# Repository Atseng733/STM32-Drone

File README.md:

# STM32 Drone
I program a drone from scratch using C++

# Hardware:

Microcontroller: STM32F103C8

IMU: MPU6050

Receiver: Flysky Fli14+

Transmitter: Flysky FS-i6

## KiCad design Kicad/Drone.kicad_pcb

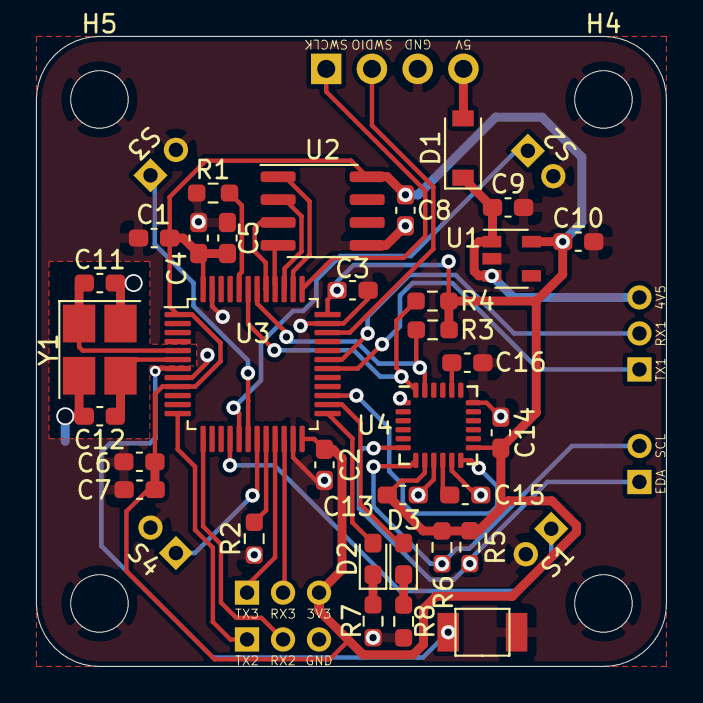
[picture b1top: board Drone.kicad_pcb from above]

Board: 2 copper layers, 35.0 x 35.0 mm, 46 parts (0 on the bottom side), 36 nets.

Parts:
C1, C2, C3, C4, C8: 100nF; C_0603_1608Metric_Pad1.08x0.95mm_HandSolder
C5: 4.7uF; C_0603_1608Metric_Pad1.08x0.95mm_HandSolder
C6, C13: 10nF; C_0603_1608Metric_Pad1.08x0.95mm_HandSolder
C7, C9, C10: 1uF; C_0603_1608Metric_Pad1.08x0.95mm_HandSolder
C11, C12: 12pF; C_0603_1608Metric_Pad1.08x0.95mm_HandSolder
C14, C15: .1uF; C_0603_1608Metric_Pad1.08x0.95mm_HandSolder
C16: 2.2nF; C_0603_1608Metric_Pad1.08x0.95mm_HandSolder
D1: ?; D_SOD-123
D2: Green; LED_0603_1608Metric_Pad1.05x0.95mm_HandSolder
D3: Red; LED_0603_1608Metric_Pad1.05x0.95mm_HandSolder
H3, H4, H5, H6: MountingHole; MountingHole_3.2mm_M3
J1: SWD; PinHeader_1x04_P2.54mm_Vertical
J2: UART1; PinHeader_1x03_P2.00mm_Vertical
J3: UART3; PinHeader_1x03_P2.00mm_Vertical
J4: UART2; PinHeader_1x03_P2.00mm_Vertical
J5: GYRO_AUX_I2C; PinHeader_1x02_P2.00mm_Vertical
R1, R2: 10k; R_0603_1608Metric_Pad0.98x0.95mm_HandSolder
R3, R4, R5, R6: 2.2k; R_0603_1608Metric_Pad0.98x0.95mm_HandSolder
R7, R8: 220; R_0603_1608Metric_Pad0.98x0.95mm_HandSolder
S1: S1; PinHeader_1x02_P2.00mm_Vertical
S2: S2; PinHeader_1x02_P2.00mm_Vertical
S3: S3; PinHeader_1x02_P2.00mm_Vertical
S4: S4; PinHeader_1x02_P2.00mm_Vertical
SW1: SW_MEC_5G; EVPBA
U1: MIC5504-3.3YM5; SOT-23-5
U2: 93CxxB; SOIC-8_3.9x4.9mm_P1.27mm
U3: STM32F103C8Tx; LQFP-48_7x7mm_P0.5mm
U4: MPU-6050; InvenSense_QFN-24_4x4mm_P0.5mm
Y1: 16 MHz; Crystal_SMD_3225-4Pin_3.2x2.5mm_HandSoldering

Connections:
4V5: C9.1, D1.1, J2.3, U1.1, U1.3
+3.3VA: C1.1, C2.1, C3.1, C4.1, C5.1, C6.1, C7.1, C8.2, C10.1, C13.1, C14.1, J3.3, R3.1, R4.1, R5.1, R6.1, U1.5, U2.8, U3.1, U3.9, U3.24, U3.36, U3.48, U4.8, U4.13
+5V: D1.2, J1.4
BOOT0: R1.1, U3.44
BOOT1: R2.1, U3.20
CS1: U2.1, U3.38
GND: C1.2, C2.2, C3.2, C4.2, C5.2, C6.2, C7.2, C8.1, C9.2, C10.2, C11.2, C12.2, C13.2, C14.2, C15.2, C16.2, H3.1, H4.1, H5.1, H6.1, J1.3, J4.3, R1.2, R2.2, R7.2, R8.2, S1.2, S2.2, S3.2, S4.2, SW1.1, U1.2, U2.5, U3.8, U3.23, U3.35, U3.47, U4.1, U4.9, U4.11, U4.18, Y1.2, Y1.4
GYRO_AUX_SCL: J5.2, R6.2, U4.7
GYRO_AUX_SDA: J5.1, R5.2, U4.6
GYRO_INT: U3.27, U4.12
HSE_IN: C11.1, U3.5, Y1.1
HSE_OUT: C12.1, U3.6, Y1.3
MISO1: U2.4, U3.40
MOSI1: U2.3, U3.41
MOTOR1_Signal: S1.1, U3.16
MOTOR2_Signal: S2.1, U3.17
MOTOR3_Signal: S3.1, U3.18
MOTOR4_Signal: S4.1, U3.19
NRST: SW1.2, U3.7
unnamed: C15.1, U4.10
unnamed: C16.1, U4.20
unnamed: D2.1, R7.1
unnamed: D2.2, U3.25
unnamed: D3.1, R8.1
unnamed: D3.2, U3.26
RX1: J2.2, U3.31
RX2: J4.2, U3.13
RX3: J3.2, U3.22
SCK1: U2.2, U3.39
SCL1: R3.2, U3.42, U4.23
SDA1: R4.2, U3.43, U4.24
SWCLK: J1.1, U3.37
SWDIO: J1.2, U3.34
TX1: J2.1, U3.30
TX2: J4.1, U3.12
TX3: J3.1, U3.21

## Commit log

2020-06-18 Create Self-balancing Drone
2020-06-22 add esp8266 project
2020-06-23 Add sigGen project
2020-06-23 Add KiCad folder to sigGen project
2020-06-24 Added working makefile
2020-06-24 Added timer functionality
2020-06-25 Working UART printc prototype
2020-06-26 Working interrupt-based USART communication
2020-06-27 USART update
2020-06-28 Added TWI interface with ssd1306 oled display + usart update
2020-06-29 Finished
2020-07-13 Added stm32 initial code
2020-08-06 added usart and gpio functionality
2020-08-06 added timer and delay
2020-08-06 added non-interrupt-based uart for use in ISRs
2020-08-06 added ssd1306 driver
2020-08-09 added boards.h for use with other stm32 boards
2020-08-16 uart rx WIP
2020-08-16 cleanup
2020-08-16 deleted unnecessary files
2020-08-16 stm32-drone readme added
2020-08-17 revamped usart and i2c
2020-08-19 basic mode prototypes
2020-09-17 new project
2020-09-19 changed usart to structure-based class
2020-09-20 updates to spi and sd card interface
2020-09-21 can now read sd card long file names(LFN)
2020-09-30 update code for less sram usage
2020-10-26 test
2020-10-29 code revamp in Test project
2020-11-01 Drone control prototype finished. Working on GPS
2020-11-03 added independent watchdog
2020-11-11 remove random prints
2020-11-12 fixed bug with yaw output and working on PID gains
2020-11-12 yaw direction fix and more pid tuning
2020-11-12 fixed issue with integrator clamping
2020-11-14 fixed bug with setpoint drift. It flies!
2020-11-14 merge
2020-11-14 changed to one project repository
2020-11-14 file directory change
2020-11-14 add files
2020-11-14 test file
